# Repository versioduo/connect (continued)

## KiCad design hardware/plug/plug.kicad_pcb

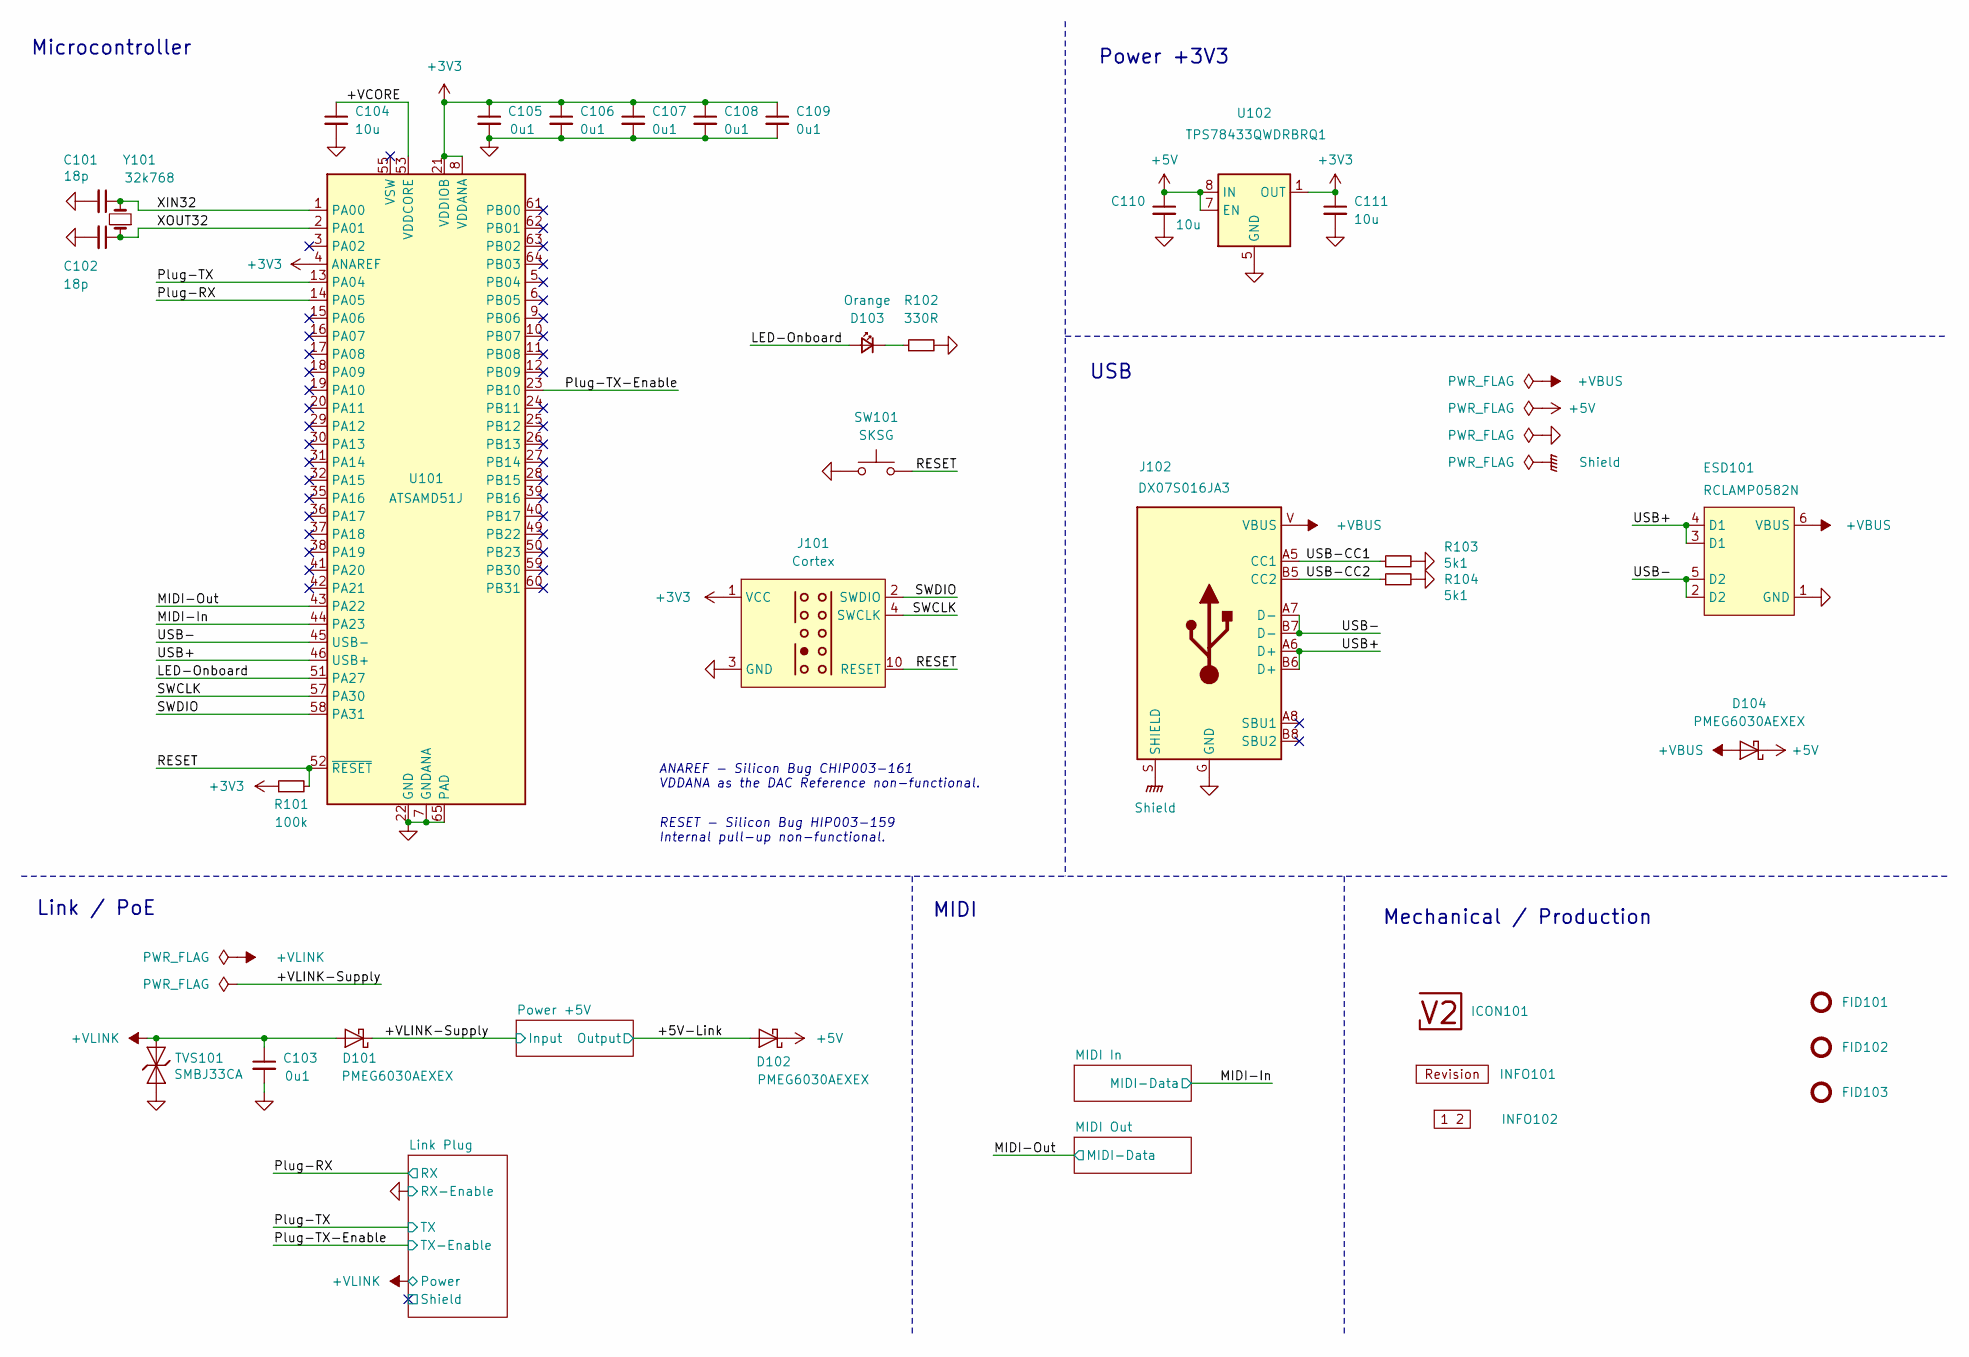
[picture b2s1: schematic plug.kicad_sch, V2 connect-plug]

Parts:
C101, C102: 18p; C_1608; Rating 50V; Mouser 810-CGA3E2C0G1H180J
C103, C105, C106, C107, C108, C109: 0u1; C_1608; Rating 50V; Mouser 810-CGA3E2X7R1H104MA
C104: 10u; C_1608; Rating 10V; Mouser 810-C1608X6S1A106M
C110, C111: 10u; C_2012; Rating 25V; Mouser 810-C2012X5R1E106K
D101, D102, D104: PMEG6030AEXEX; D_SOD-123HP; Rating 60V; Mouser 771-PMEG6030AEXEX
D103: Orange; LED_1608; Rating 605nm; Mouser 755-SML-D12D1WT86
ESD101: RCLAMP0582N; SLP1210N6; Rating 20kV; Mouser 947-RCLAMP0582N.TCT
FID101, FID102, FID103: Fiducial_Paste; Fiducial_0.5mm_Mask1mm_Paste
ICON101: V2-logo; Logo_Small
INFO101: Revision
INFO102: Layer_Numbers-4
J101: Cortex
J102: DX07S016JA3; JAE_DX07S016JA3; Rating USB2.0; Mouser 656-DX07S016JA3R1500
R101: 100k; R_1608; Rating 100mW; Mouser 71-CRCW0603100KFKEAC
R102: 330R; R_1608; Rating 100mW; Mouser 71-CRCW0603330RFKEAC
R103, R104: 5k1; R_1608; Rating 100mW; Mouser 71-CRCW06035K10FKEAC
SW101: SKSG; Rating 1.6N; Mouser 688-SKSGACE010
TVS101: SMBJ33CA; D_SMB; Rating 33V; Mouser 652-SMBJ33CA-Q
U101: ATSAMD51J; QFN-64-1EP_9x9mm_P0.5mm_EP4.8x4.8mm_ThermalVias; Rating Cortex-M4F; Mouser 556-ATSAMD51J19AMU
U102: TPS78433QWDRBRQ1; VSON-8-1_3x3mm_P0.65_EP1.65x2.4mm; Rating 300mA; Mouser 595-TPS78433QWDRBRQ1
Y101: 32k768; Crystal_SMD_3215-2Pin_3.2x1.5mm; Rating 10ppm; Mouser 815-ABS0716632.768KT

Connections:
+3V3: C105.1, C106.1, C107.1, C108.1, C109.1, C111.1, J101.1 (VCC), R101.1, U101.4 (ANAREF), U101.8 (VDDANA), U101.21 (VDDIOB), U101.34 (VDDIO), U101.48 (VDDIO), U101.56 (VDDIO), U102.1 (OUT); also elsewhere on the board
+5V: C110.1, D102.1 (K), D104.1 (K), U102.7 (EN), U102.8 (IN); also elsewhere on the board
/+5V-Link: D102.2 (A); also elsewhere on the board
/+VBUS: D104.2 (A), ESD101.6 (VBUS), J102.V (VBUS)
/+VCORE: C104.1, U101.53 (VDDCORE)
/+VLINK: C103.1, D101.2 (A), TVS101.2 (A); also elsewhere on the board
/+VLINK-Supply: D101.1 (K); also elsewhere on the board
/LED-Onboard: D103.2 (A), U101.51 (PA27)
/MIDI-In: U101.44 (PA23); also elsewhere on the board
/MIDI-Out: U101.43 (PA22); also elsewhere on the board
/Plug-RX: U101.14 (PA05); also elsewhere on the board
/Plug-TX: U101.13 (PA04); also elsewhere on the board
/Plug-TX-Enable: U101.23 (PB10); also elsewhere on the board
/RESET: J101.10 (RESET), R101.2, SW101.2, U101.52 (~RESET)
/SWCLK: J101.4 (SWCLK), U101.57 (PA30)
/SWDIO: J101.2 (SWDIO), U101.58 (PA31)
/Shield: J102.S (SHIELD)
/USB+: ESD101.3 (D1), ESD101.4 (D1), J102.A6 (D+), J102.B6 (D+), U101.46 (USB+)
/USB-: ESD101.2 (D2), ESD101.5 (D2), J102.A7 (D-), J102.B7 (D-), U101.45 (USB-)
/USB-CC1: J102.A5 (CC1), R103.1
/USB-CC2: J102.B5 (CC2), R104.1
/XIN32: C101.1, U101.1 (PA00), Y101.2
/XOUT32: C102.1, U101.2 (PA01), Y101.1
GND: C101.2, C102.2, C103.2, C104.2, C105.2, C106.2, C107.2, C108.2, C109.2, C110.2, C111.2, ESD101.1 (GND), J101.3 (GND), J101.5 (GND), J102.G (GND), R102.2, R103.2, R104.2, SW101.1, TVS101.1 (K), U101.7 (GNDANA), U101.22 (GND), U101.33 (GND), U101.47 (GND), U101.54 (GND), U101.65 (PAD), U102.5 (GND), U102.9 (GND); also elsewhere on the board
unnamed: D103.1 (K), R102.1

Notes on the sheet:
ANAREF - Silicon Bug CHIP003-161 VDDANA as the DAC Reference non-functional.
Link / PoE
RESET - Silicon Bug HIP003-159 Internal pull-up non-functional.
MIDI
Power +3V3
Mechanical / Production
Microcontroller
USB

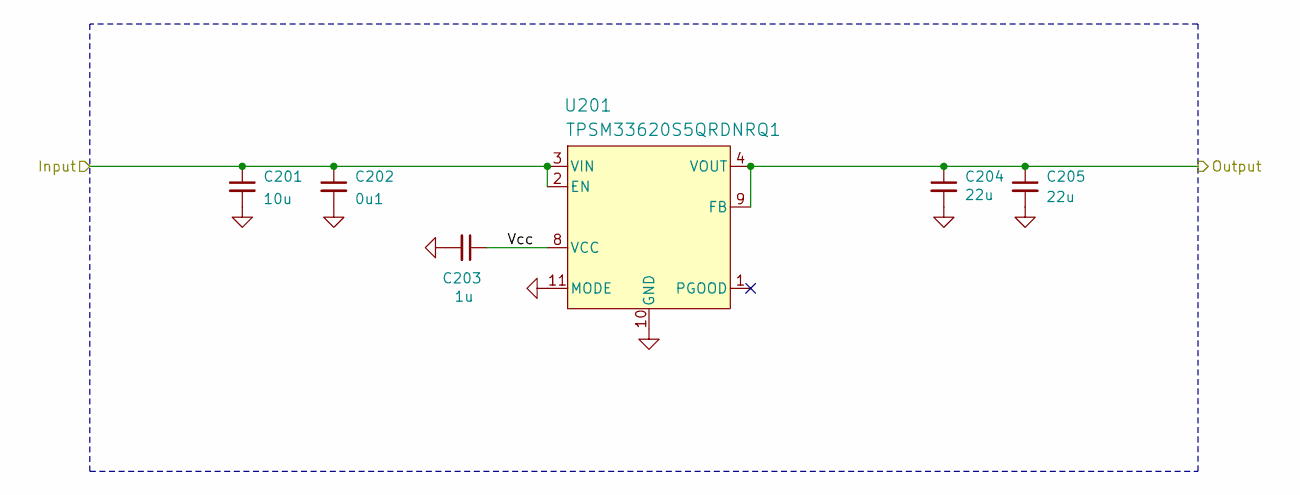
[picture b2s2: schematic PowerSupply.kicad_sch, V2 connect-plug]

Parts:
C201: 10u; C_3225; Rating 50V; Mouser 810-CNC6P1X7R1H106K2
C202: 0u1; C_1608; Rating 50V; Mouser 810-CGA3E2X7R1H104MA
C203: 1u; C_1608; Rating 50V; Mouser 810-CGA3E3X7R1H105K0
C204, C205: 22u; C_3225; Rating 25V; Mouser 810-CGA6P3X7R1E226M5
U201: TPSM33620S5QRDNRQ1; QFN-11; Rating 2A; Mouser 595-SM33620S5QRDNRQ1

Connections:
/+5V-Link: C204.1, C205.1, U201.4 (VOUT), U201.9 (FB); also elsewhere on the board
/+VLINK-Supply: C201.1, C202.1, U201.2 (EN), U201.3 (VIN); also elsewhere on the board
/Power +5V/Vcc: C203.1, U201.8 (VCC)
GND: C201.2, C202.2, C203.2, C204.2, C205.2, U201.10 (GND), U201.11 (MODE); also elsewhere on the board

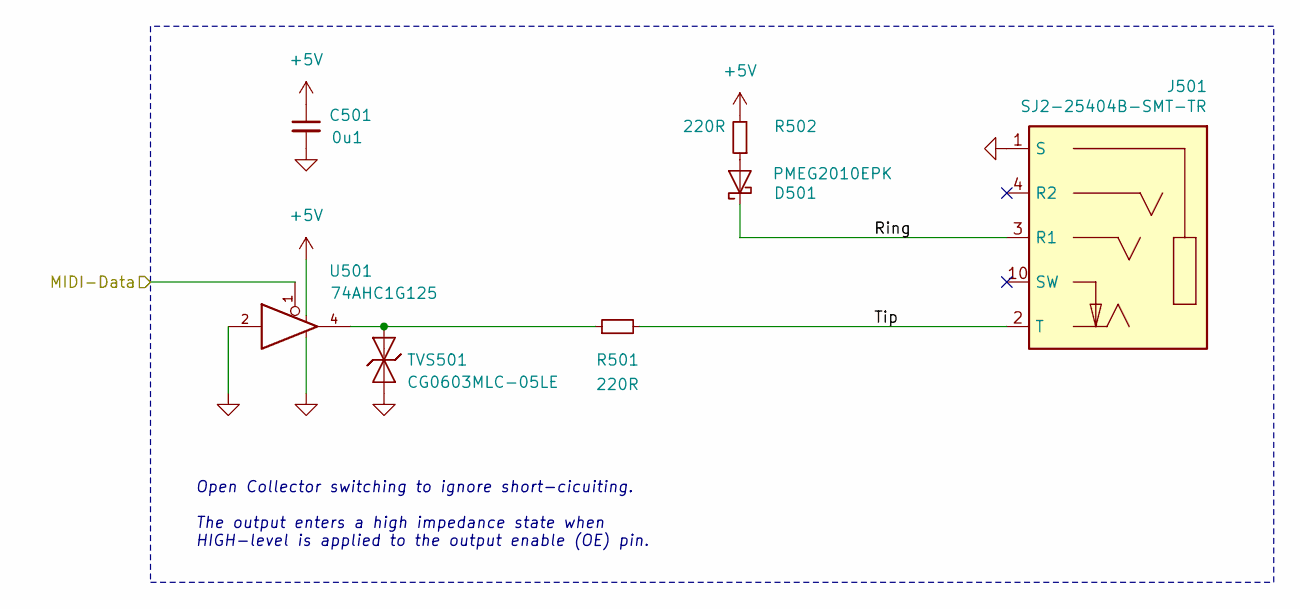
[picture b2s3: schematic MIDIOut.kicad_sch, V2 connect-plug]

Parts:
C501: 0u1; C_1608; Rating 50V; Mouser 810-CGA3E2X7R1H104MA
D501: PMEG2010EPK; D_SOD-1608; Rating 20V; Mouser 771-PMEG2010EPK
J501: SJ2-25404B-SMT-TR; CUI_SJ2-25404B-SMT-TR; Rating 2.5mm; Mouser 490-SJ2-25404BSMT-TR
R501, R502: 220R; R_1608; Rating 330mW; Mouser 71-CRCW0603220RFKEAH
TVS501: CG0603MLC-05LE; D_1608; Rating 5V; Mouser 652-CG0603MLC-05LE
U501: 74AHC1G125; SOT-23-5; Rating 8mA; Mouser 595-SN74AHC1G125DBVR

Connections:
+5V: C501.1, R502.2, U501.5; also elsewhere on the board
/MIDI Out/Ring: D501.1 (K), J501.3 (R1)
/MIDI Out/Tip: J501.2 (T), R501.2
/MIDI-Out: U501.1; also elsewhere on the board
GND: C501.2, J501.1 (S), TVS501.1 (K), U501.2, U501.3; also elsewhere on the board
unnamed: D501.2 (A), R502.1
unnamed: R501.1, TVS501.2 (A), U501.4

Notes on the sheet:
﻿Open Collector switching to ignore short-cicuiting. The output enters a high impedance state when HIGH-level is applied to the output enable (OE) pin.

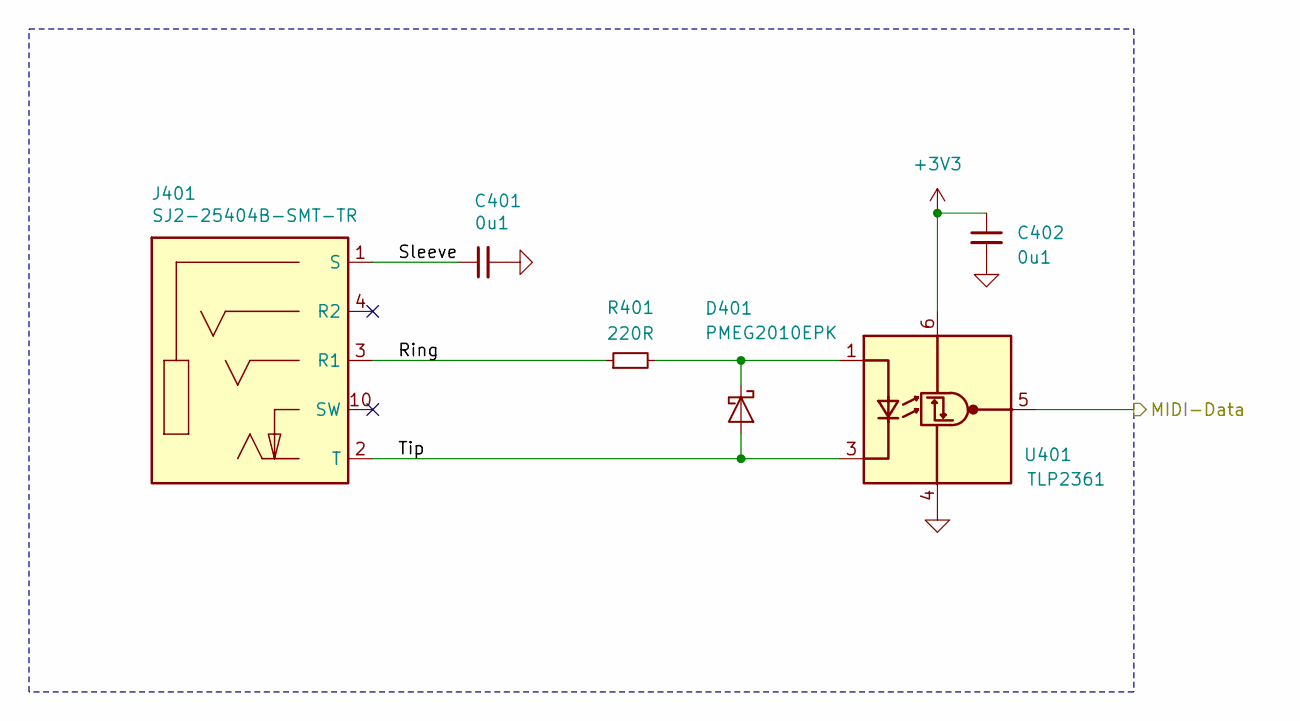
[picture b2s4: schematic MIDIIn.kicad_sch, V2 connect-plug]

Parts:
C401, C402: 0u1; C_1608; Rating 50V; Mouser 810-CGA3E2X7R1H104MA
D401: PMEG2010EPK; D_SOD-1608; Rating 20V; Mouser 771-PMEG2010EPK
J401: SJ2-25404B-SMT-TR; CUI_SJ2-25404B-SMT-TR; Rating 2.5mm; Mouser 490-SJ2-25404BSMT-TR
R401: 220R; R_1608; Rating 330mW; Mouser 71-CRCW0603220RFKEAH
U401: TLP2361; SO-5-6_4.55x3.7mm_P1.27mm; Rating 15Mbps; Mouser 757-TLP2361TPRE

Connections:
+3V3: C402.1, U401.6 (VDD); also elsewhere on the board
/MIDI In/Ring: J401.3 (R1), R401.1
/MIDI In/Sleeve: C401.1, J401.1 (S)
/MIDI In/Tip: D401.2 (A), J401.2 (T), U401.3 (K)
/MIDI-In: U401.5 (VO); also elsewhere on the board
GND: C401.2, C402.2, U401.4 (GND); also elsewhere on the board
unnamed: D401.1 (K), R401.2, U401.1 (A)

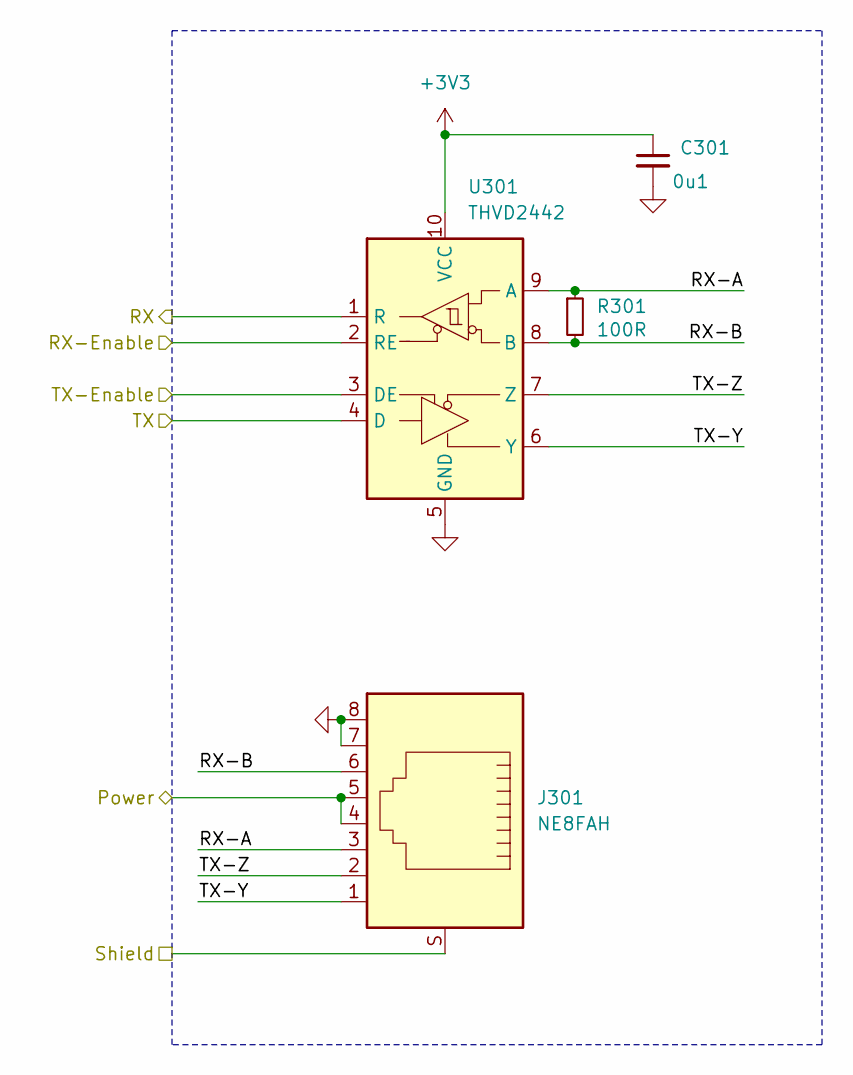
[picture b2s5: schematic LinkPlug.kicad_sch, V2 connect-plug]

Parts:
C301: 0u1; C_1608; Rating 50V; Mouser 810-CGA3E2X7R1H104MA
J301: NE8FAH; Rating CAT5e; Mouser 568-NE8FAH
R301: 100R; R_1608; Rating 330mW; Mouser 71-CRCW0603100RFKEAH
U301: THVD2442; VSON-10-4-1EP_3x3mm_P0.5mm_EP1.65x2.4mm_ThermalVias; Rating 20Mbps; Mouser 595-THVD2442DRCR

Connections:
+3V3: C301.1, U301.10 (VCC); also elsewhere on the board
/+VLINK: J301.4, J301.5; also elsewhere on the board
/Link Plug/RX-A: J301.3, R301.1, U301.9 (A)
/Link Plug/RX-B: J301.6, R301.2, U301.8 (B)
/Link Plug/Shield: J301.S
/Link Plug/TX-Y: J301.1, U301.6 (Y)
/Link Plug/TX-Z: J301.2, U301.7 (Z)
/Plug-RX: U301.1 (R); also elsewhere on the board
/Plug-TX: U301.4 (D); also elsewhere on the board
/Plug-TX-Enable: U301.3 (DE); also elsewhere on the board
GND: C301.2, J301.7, J301.8, U301.2 (RE), U301.5 (GND), U301.11 (GND); also elsewhere on the board

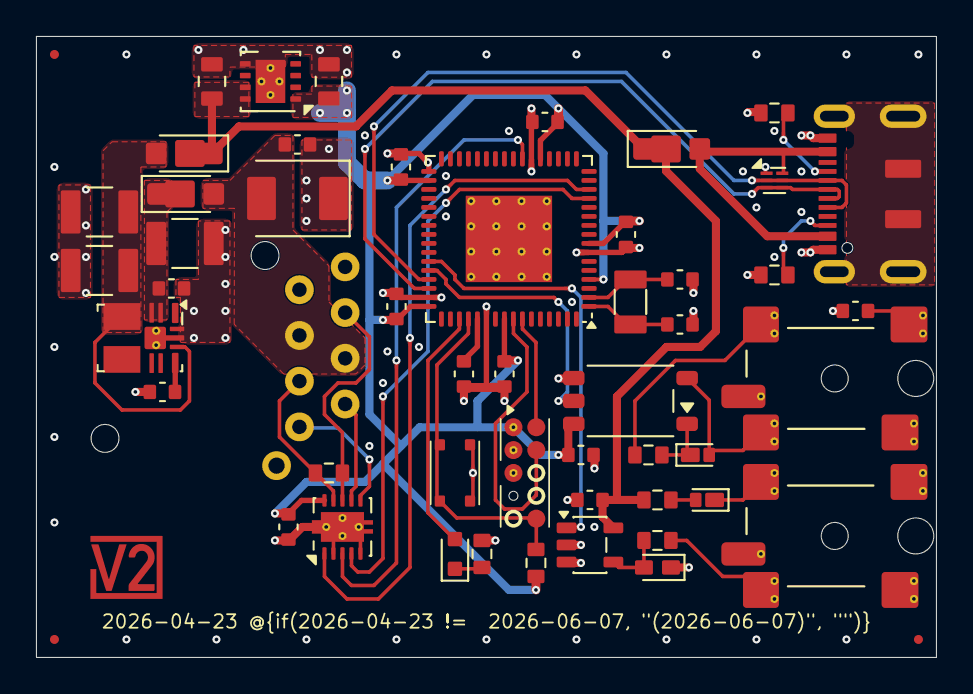
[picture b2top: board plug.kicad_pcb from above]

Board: 4 copper layers, 50.0 x 34.5 mm, 56 parts (1 on the bottom side), 37 nets.

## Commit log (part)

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2021-09-22 Import
2026-02-01 Update library
2026-02-10 Refresh
2026-02-10 Use date as revision
2026-02-13 Replace Order_Number
2026-03-02 Export stencil
2026-03-12 Replace diode
2026-03-14 Update ESD suppressor
2026-03-21 KiCad 10
2026-03-29 Update Revision footprint
2026-03-31 Replace step-down
2026-04-23 Split into socket and plug
2026-04-24 Update DRC
2026-05-11 Good Bye Imperial
2026-05-19 Add plug firmware
2026-05-19 Add connect-socket firmware
2026-05-22 connect-socket: CC LED splash
2026-06-21 Update MIDI API
2026-06-23 Update V2MIDI API
